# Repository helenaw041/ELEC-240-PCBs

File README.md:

# ELEC-240-PCBs
Make any PCB related to Halloween or Christmas with at least 1 IC!

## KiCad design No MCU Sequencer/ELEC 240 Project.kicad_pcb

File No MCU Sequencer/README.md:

I designed a sequencer on a 2"x2" PCB with 555 timers and SISO shift registers! 
The user can input up to 8 notes in the shift register and play them back at an adjustable speed (0.8754Hz to 2Hz) with the potentiometer. 
The three 555 timers are for clocking in current input notes, setting the playback frequency, and outputting the notes stored in the shift registers. 
I currently have one shift register for each note. 

**TO USE:**
Loop the 3 notes for a spooky tune! Use record button to clock in notes. 

**FUTURE IMPROVEMENTS:**
- If I get a decoder, I can use each shift register to represent one bit of information and can actually represent 8 notes with only 3 shift registers!
- No decoder--possibly implement an R2R DAC with an antilog amplifier to create a full scale of notes?
- Find more slide switches...to replace the push buttons for the notes
- Add an audio amplifier

**Detailed Description:**
I designed a simple sequencer using 3 shift registers and 3 555 timers, where the user is able to “store” up to eight “beats” from a selection of three distinct notes in the SISO shift registers in the pulse mode and play them back at a configurable frequency in the playback mode. 

Each shift register stores the memory of one note and is configured to “correspond to” one of three notes: A3, C4, and D#4. When these notes are played in sequence, it should output a spooky tune. 

The first 555 timer is configured in its monostable mode, with a pulse width of 1.1(1kOhm)(1uF) = 110ms. I chose these specific values so that the pulse width would be longer than the time it takes for the button to settle after debouncing. The purpose of this component lies in the functionality of the SPDT switch (which I call the mode switch) connected to the SRCLKpin 11 input of the shift registers connected to it, which toggles between two modes: pulse mode and playback mode. 

When the mode switch is toggled to pulse mode and the button connected to this timer is pressed, the current state of the push buttons associated with each shift register/note are clocked in. 

The second 555 timer is configured in astable mode, with a variable frequency of 0.8754Hz to 2Hz because of the 10k potentiometer as our R2 in this formula:

When the mode switch is toggled to playback mode, notes will play back at this specified frequency. 

The third 555 timer controls the tone of the outputted notes. When the mode switch is toggled to pulse mode, the state of the push buttons connected to each shift register controls whether a “play” or “silent” signal gets stored in the shift register for the corresponding note. When the mode switch is toggled to playback mode, the output of the shift registers determines whether the corresponding nMOS gate for each tone is open or closed. 

To elaborate on the input to SERpin 14 for the shift registers: When the 555 timer is in pulse mode, SERpin 14 takes the button input branch as its input. When the 555 timer is in playback mode, SERpin 14 takes the output of QH’pin 9 as its input (it loops the values stored in the shift register). This is controlled via the SPDT switches connected to each shift register.

The reset button resets the shift registers. 

Let us say that we want to play a simple sequence of notes: A3, C4, D#4, silence, A3, C4, D#4, silence. Because the shift register can only store eight bits of data, the melody will loop once these eight notes have been played. 
1. Ensure all 4 SPDT switches are toggled to pulse/record mode. Also press the reset button to ensure the shift registers are fully cleared. 
2. Press down on the push button corresponding to the note A3, and without releasing it, press down on the push button connected to the first 555 timer to send a pulse to the shift registers. Because A3 is the only button pressed down, a ‘1’ will be clocked into the 8th bit slot of the A3 shift register. 
3. Now release all buttons. Press down on the push button corresponding to C4, and clock it in the same way as in step 2. Now, a ‘1’ will be clocked into the 8th bit slot of the C4 shift register. The bit in ‘A3’ will “move up” to the 7th slot. 
4. Now repeat this until the remaining 6 notes are clocked into the shift registers. 
5. Toggle the three SPDT switches connected to the shift registers to playback mode now in no particular order. This means that the shift registers will no longer take inputs from the corresponding buttons but will loop the data already stored in them.
6. Now flip the SPDT switch connected to the SRCLKpin 11 input to playback mode so that notes are clocked in periodically at a frequency corresponding to that of the playback frequency of the second shift register.
7. The inputted notes should now loop until the reset button is pressed or power is disconnected!

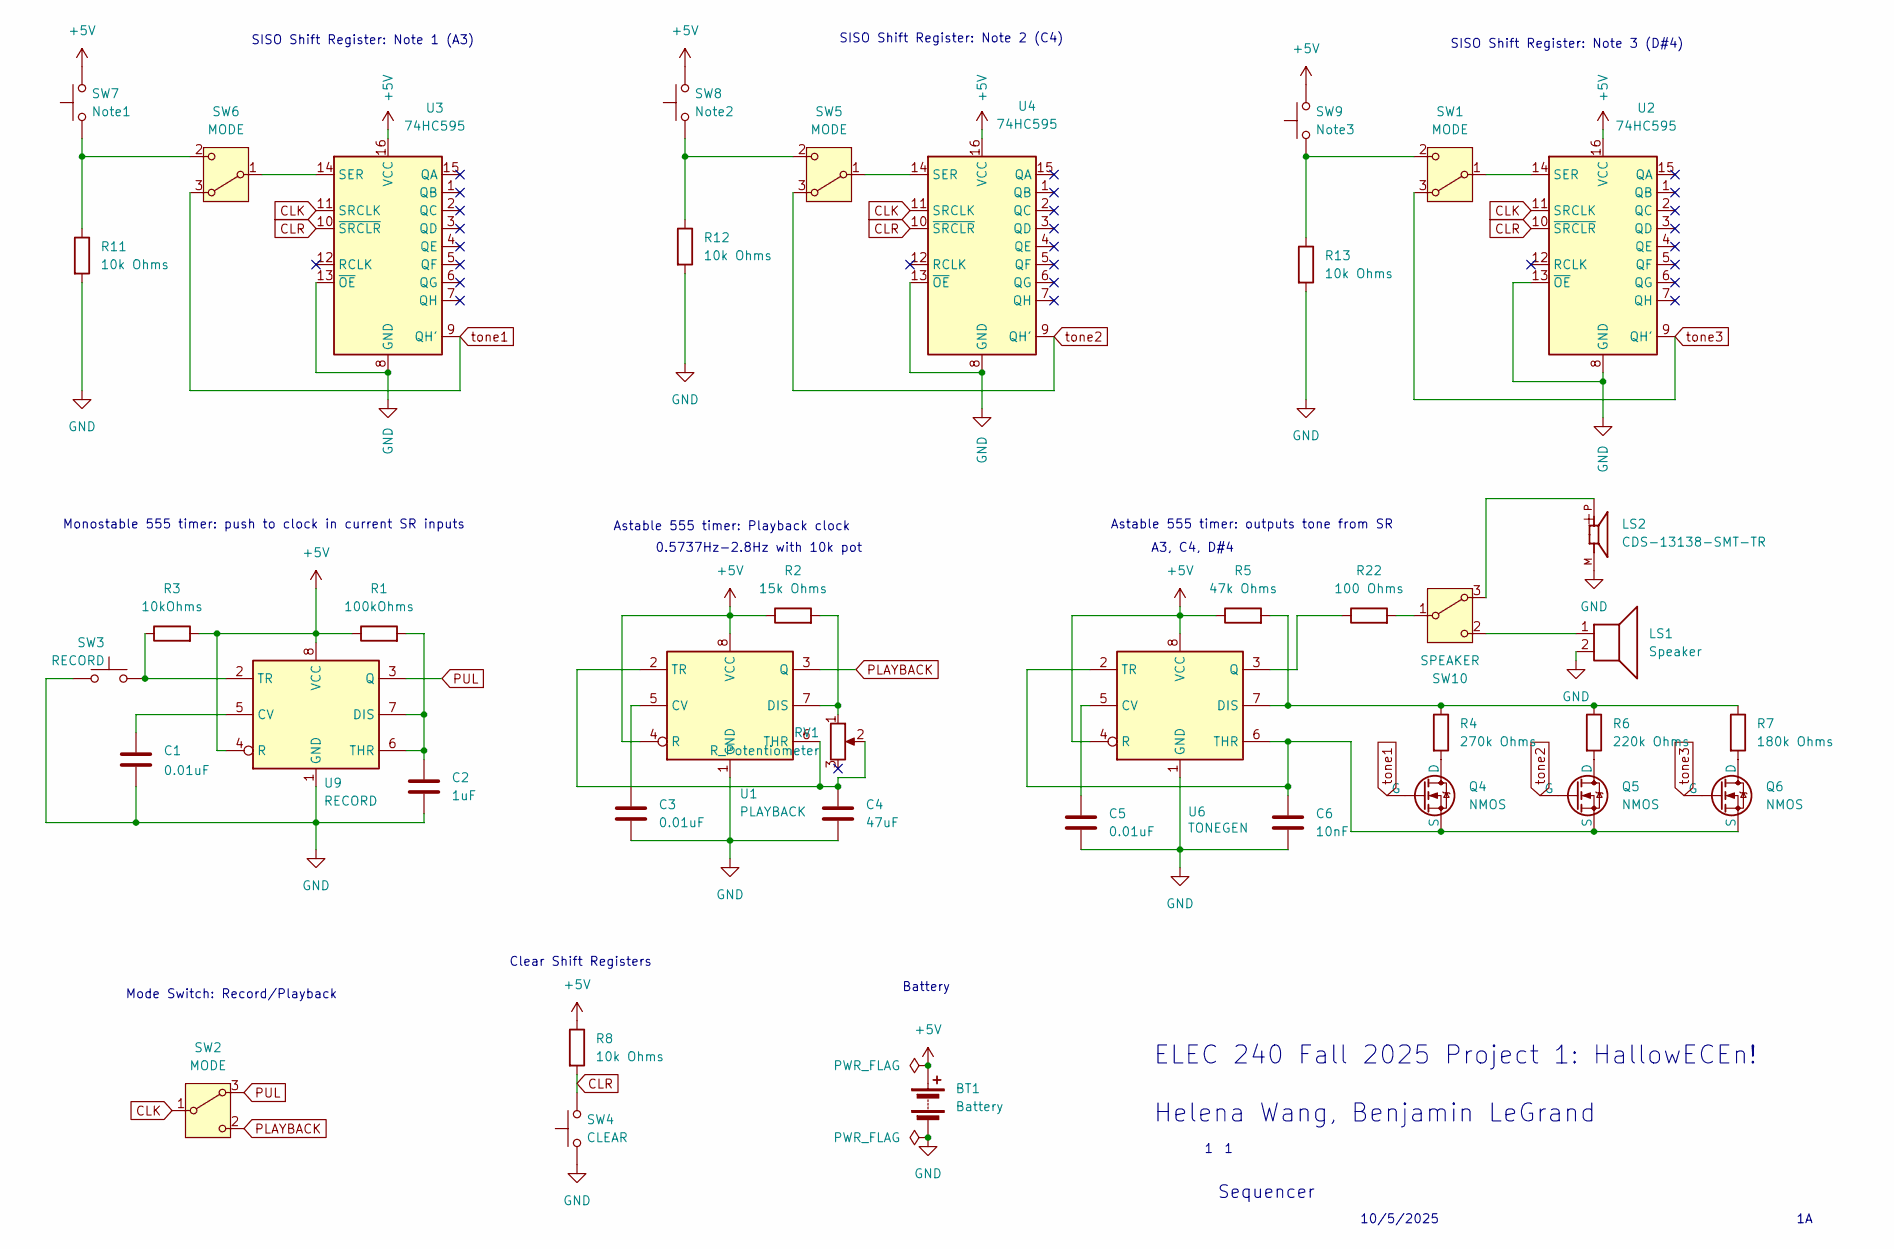
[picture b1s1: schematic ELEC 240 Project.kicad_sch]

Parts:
BT1: Battery; PinHeader_2x01_P2.00mm_Vertical
C1, C3, C5: 0.01uF; C_Disc_D4.3mm_W1.9mm_P5.00mm
C2: 1uF; C_Disc_D4.3mm_W1.9mm_P5.00mm
C4: 47uF; C_Disc_D4.3mm_W1.9mm_P5.00mm
C6: 10nF; C_Disc_D4.3mm_W1.9mm_P5.00mm
LS1: Speaker; PinHeader_2x01_P2.00mm_Vertical
LS2: CDS-13138-SMT-TR; SPKR_CDS-13138-SMT-TR
Q4, Q5, Q6: NMOS; PinHeader_1x03_P2.54mm_Vertical
R1: 100kOhms; R_Axial_DIN0204_L3.6mm_D1.6mm_P5.08mm_Horizontal
R2: 15k Ohms; R_Axial_DIN0204_L3.6mm_D1.6mm_P5.08mm_Horizontal
R3: 10kOhms; R_Axial_DIN0204_L3.6mm_D1.6mm_P5.08mm_Horizontal
R4: 270k Ohms; R_Axial_DIN0204_L3.6mm_D1.6mm_P5.08mm_Horizontal
R5: 47k Ohms; R_Axial_DIN0204_L3.6mm_D1.6mm_P5.08mm_Horizontal
R6: 220k Ohms; R_Axial_DIN0204_L3.6mm_D1.6mm_P5.08mm_Horizontal
R7: 180k Ohms; R_Axial_DIN0204_L3.6mm_D1.6mm_P5.08mm_Horizontal
R8, R11, R12, R13: 10k Ohms; R_Axial_DIN0204_L3.6mm_D1.6mm_P5.08mm_Horizontal
R22: 100 Ohms; R_Axial_DIN0204_L3.6mm_D1.6mm_P5.08mm_Horizontal
RV1: R_Potentiometer; Potentiometer_ACP_CA9-H2,5_Horizontal
SW1, SW2, SW5, SW6: MODE; SW_Slide-03_Wuerth-WS-SLTV_10x2.5x6.4_P2.54mm
SW3: RECORD; SW_PUSH_6mm
SW4: CLEAR; SW_PUSH_6mm
SW7: Note1; SW_PUSH_6mm
SW8: Note2; SW_PUSH_6mm
SW9: Note3; SW_PUSH_6mm
SW10: SPEAKER; SW_Slide-03_Wuerth-WS-SLTV_10x2.5x6.4_P2.54mm
U1: PLAYBACK; DIP-8_W7.62mm_Socket
U2, U3, U4: 74HC595; DIP-16_W10.16mm
U6: TONEGEN; DIP-8_W7.62mm_Socket
U9: RECORD; DIP-8_W7.62mm_Socket

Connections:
+5V: BT1.1 (+), R1.1, R2.1, R3.2, R5.1, R8.1, SW7.2, SW8.2, SW9.2, U1.4 (R), U1.8 (VCC), U2.16 (VCC), U3.16 (VCC), U4.16 (VCC), U6.4 (R), U6.8 (VCC), U9.4 (R), U9.8 (VCC)
CLK: SW2.1 (B), U2.11 (SRCLK), U3.11 (SRCLK), U4.11 (SRCLK)
CLR: R8.2, SW4.2, U2.10 (~SRCLR), U3.10 (~SRCLR), U4.10 (~SRCLR)
GND: BT1.2 (-), C1.1, C2.2, C3.2, C4.2, C5.2, C6.2, LS1.2, LS2.M, R11.2, R12.2, R13.2, SW3.1, SW4.1, U1.1 (GND), U2.8 (GND), U2.13 (~OE), U3.8 (GND), U3.13 (~OE), U4.8 (GND), U4.13 (~OE), U6.1 (GND), U9.1 (GND)
unnamed: Q4.1 (D), R4.2
unnamed: C6.1, Q4.3 (S), Q5.3 (S), Q6.3 (S), U6.2 (TR), U6.6 (THR)
unnamed: Q5.1 (D), R6.2
unnamed: Q6.1 (D), R7.2
unnamed: SW1.1 (B), U2.14 (SER)
unnamed: R13.1, SW1.2 (C), SW9.1
unnamed: SW5.1 (B), U4.14 (SER)
unnamed: R12.1, SW5.2 (C), SW8.1
unnamed: SW6.1 (B), U3.14 (SER)
unnamed: R11.1, SW6.2 (C), SW7.1
unnamed: LS2.P, SW10.3 (A)
unnamed: R22.2, SW10.1 (B)
unnamed: LS1.1, SW10.2 (C)
unnamed: C3.1, U1.5 (CV)
unnamed: R2.2, RV1.1, U1.7 (DIS)
unnamed: C4.1, RV1.2, U1.2 (TR), U1.6 (THR)
unnamed: C5.1, U6.5 (CV)
unnamed: R4.1, R5.2, R6.1, R7.1, U6.7 (DIS)
unnamed: R22.1, U6.3 (Q)
unnamed: C1.2, U9.5 (CV)
unnamed: C2.1, R1.2, U9.6 (THR), U9.7 (DIS)
unnamed: R3.1, SW3.2, U9.2 (TR)
PLAYBACK: SW2.2 (C), U1.3 (Q)
PUL: SW2.3 (A), U9.3 (Q)
tone1: Q4.2 (G), SW6.3 (A), U3.9 (QH')
tone2: Q5.2 (G), SW5.3 (A), U4.9 (QH')
tone3: Q6.2 (G), SW1.3 (A), U2.9 (QH')

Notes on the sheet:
A3, C4, D#4
Mode Switch: Record/Playback
Monostable 555 timer: push to clock in current SR inputs
Battery
ELEC 240 Fall 2025 Project 1: HallowECEn! Helena Wang, Benjamin LeGrand
Astable 555 timer: Playback clock
0.5737Hz-2.8Hz with 10k pot
Astable 555 timer: outputs tone from SR
Sequencer
SISO Shift Register: Note 2 (C4)
SISO Shift Register: Note 1 (A3)
10/5/2025
Clear Shift Registers
SISO Shift Register: Note 3 (D#4)

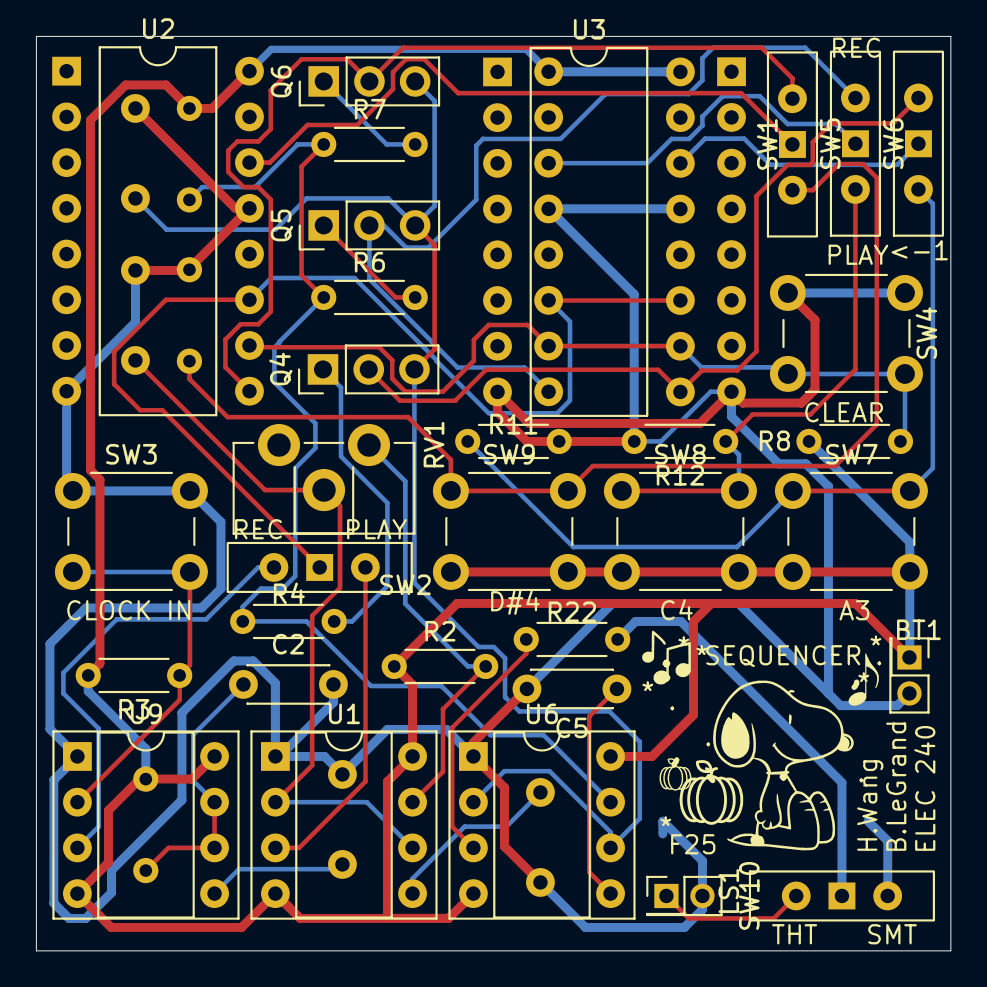
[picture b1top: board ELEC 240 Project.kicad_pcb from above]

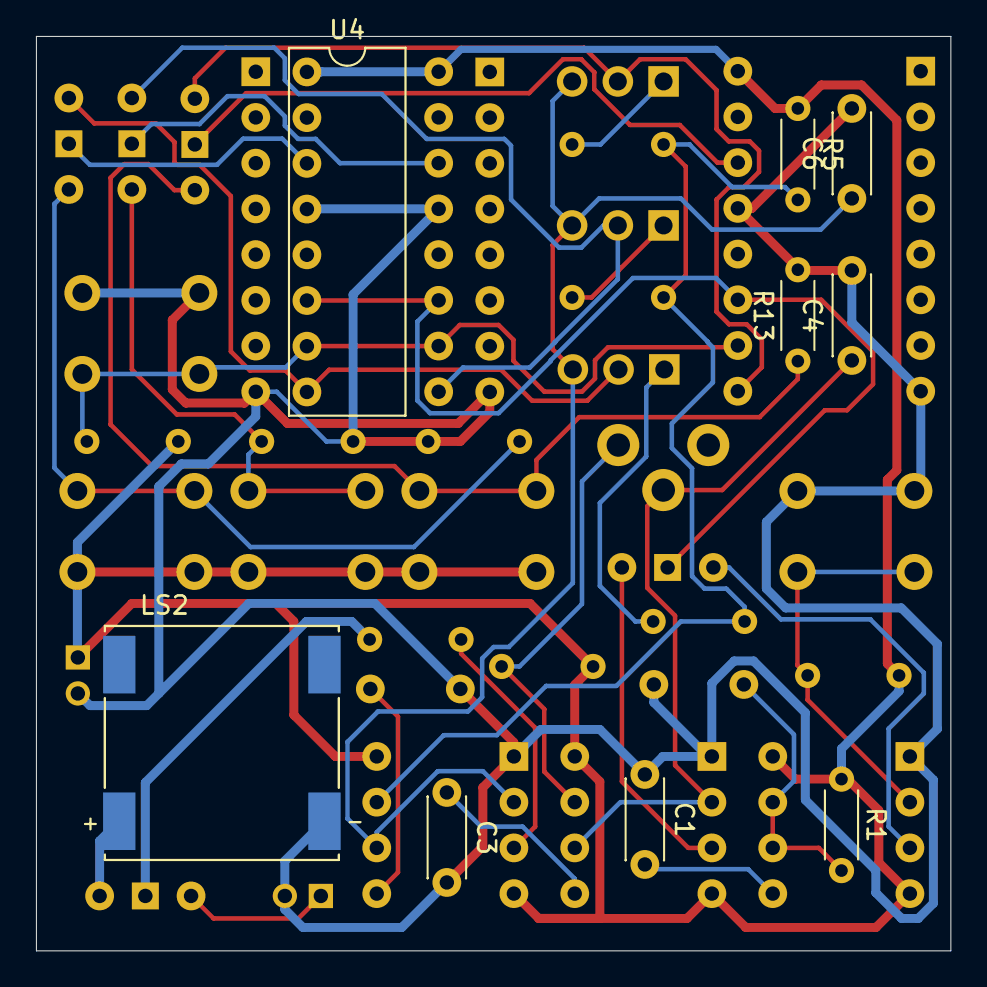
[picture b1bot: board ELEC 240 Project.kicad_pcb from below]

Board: 2 copper layers, 50.8 x 50.8 mm, 46 parts (9 on the bottom side), 31 nets.

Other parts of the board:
': LOGO
,: LOGO
.: LOGO
:: LOGO
`: LOGO

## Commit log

2025-10-17 Create docs
